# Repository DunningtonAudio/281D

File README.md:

# 281D
A quad function generator project

The 281D Quad Function Generator is designed to replicate the functionality of the Buchla 281 module using modern construction techniques and readily available parts. It is primarily based on the original circuit designed by Don Buchla, with the following additions/alterations:

* Improved input and mode selection circuitry – no requirement to “kick” the generators when selecting self cycle mode.
* All outputs are buffered, protecting the integrator core and passive end pulse generation from the effects of loading when stacked to multiple inputs.
* End pulse outputs are designed to allow stacking of multiple outputs to a single input without affecting cycling of individual generators, allowing the creation of complex/non-repeating/polyrhythmic pulse sequences. Unlike other solutions that simply add a diode in series with the output, the 281D end pulse outputs can drive a floating input low.
 
There are several build options to adjust the function of the module to a particular users requirements.

The repository contains:

* KiCad project files.
* Schematic and build/calibration notes as PDF files.
* Bill of Materials in ODS format.
* Interactive webpage for matching BOM items to PCB locations.

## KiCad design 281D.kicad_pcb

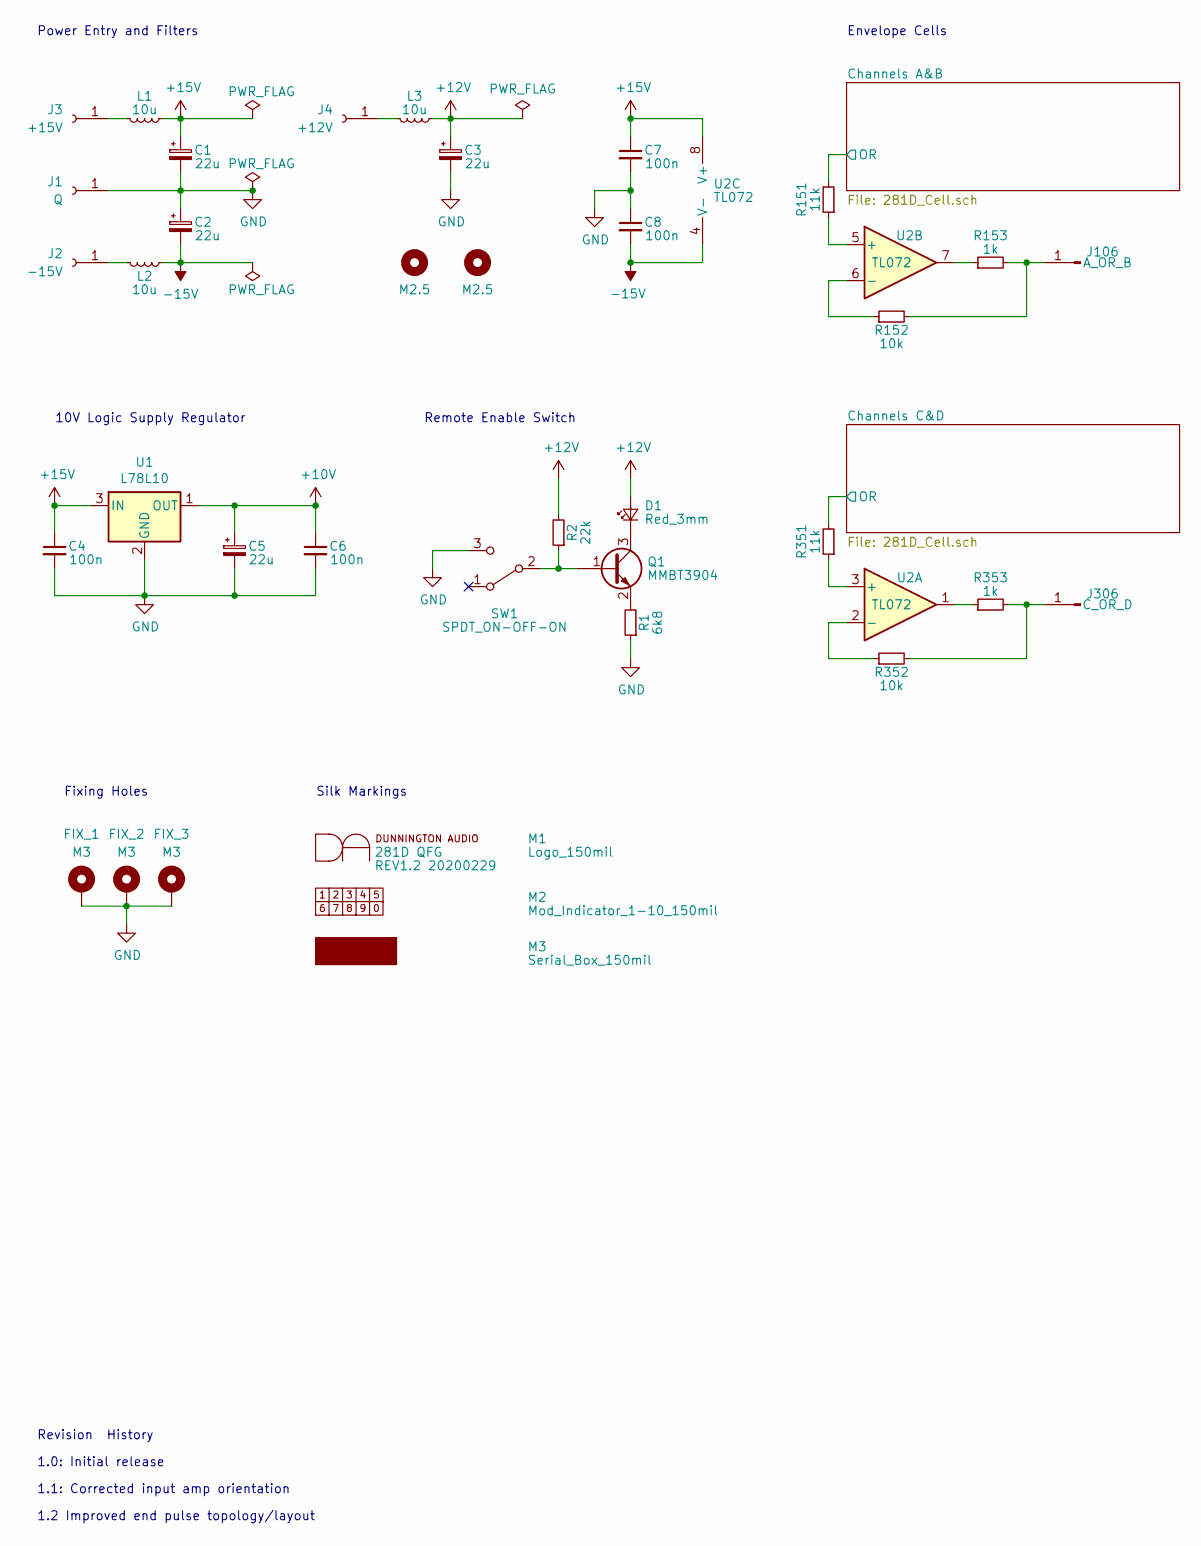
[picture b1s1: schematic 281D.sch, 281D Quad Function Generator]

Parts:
C1, C2, C3, C5: 22u; CP_Elec_5x5.3
C4, C6, C7, C8: 100n; C_0805_2012Metric
D1: Red_3mm; LED_D3.0mm
FIX_1, FIX_2, FIX_3: M3; MountingHole_3.2mm_M3_Pad_Via
H101, H102: M2.5; MountingHole_2.5mm
J1: Q; SolderWirePad_1x01_Drill1.2mm
J2: -15V; SolderWirePad_1x01_Drill1.2mm
J3: +15V; SolderWirePad_1x01_Drill1.2mm
J4: +12V; SolderWirePad_1x01_Drill1.2mm
J106, J306: 108-0910-001; Johnson_108-09XX-001
L1, L2, L3: 10u; L_0805_2012Metric
M1: Logo_150mil
M2: Mod_Indicator_1-10_150mil
M3: Serial_Box_150mil
Q1: MMBT3904; SOT-23
R1: 6k8; R_0805_2012Metric
R2: 22k; R_0805_2012Metric
R151, R351: 11k; R_0805_2012Metric
R152, R352: 10k; R_0805_2012Metric
R153, R353: 1k; R_0805_2012Metric
SW1: SPDT_ON-OFF-ON; M201xSS1x01
U1: L78L10; SOT-89-3
U2: TL072; SOIC-8_3.9x4.9mm_P1.27mm

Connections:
+10V: C5.1, C6.1, U1.1 (OUT); also elsewhere on the board
+12V: C3.1, D1.2 (A), L3.1, R2.2; also elsewhere on the board
+15V: C1.1, C4.1, C7.1, L1.1, U1.3 (IN), U2.8 (V+); also elsewhere on the board
-15V: C2.2, C8.2, L2.1, U2.4 (V-); also elsewhere on the board
/Channels A&B/OR: R151.2; also elsewhere on the board
/Channels C&D/OR: R351.2; also elsewhere on the board
GND: C1.2, C2.1, C3.2, C4.2, C5.2, C6.2, C7.2, C8.1, FIX_1.1, FIX_2.1, FIX_3.1, J1.1, R1.1, SW1.3 (C), U1.2 (GND); also elsewhere on the board
unnamed: D1.1 (K), Q1.3 (C)
unnamed: J2.1, L2.2
unnamed: J3.1, L1.2
unnamed: J4.1, L3.2
unnamed: J106.1, R152.2, R153.2
unnamed: J306.1, R352.2, R353.2
unnamed: Q1.1 (B), R2.1, SW1.2 (B)
unnamed: Q1.2 (E), R1.2
unnamed: R151.1, U2.5 (+)
unnamed: R152.1, U2.6 (-)
unnamed: R153.1, U2.7
unnamed: R351.1, U2.3 (+)
unnamed: R352.1, U2.2 (-)
unnamed: R353.1, U2.1

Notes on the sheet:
Envelope Cells
Power Entry and Filters
10V Logic Supply Regulator
Remote Enable Switch
Fixing Holes
Revision History
1.0: Initial release
1.1: Corrected input amp orientation
1.2 Improved end pulse topology/layout
Silk Markings

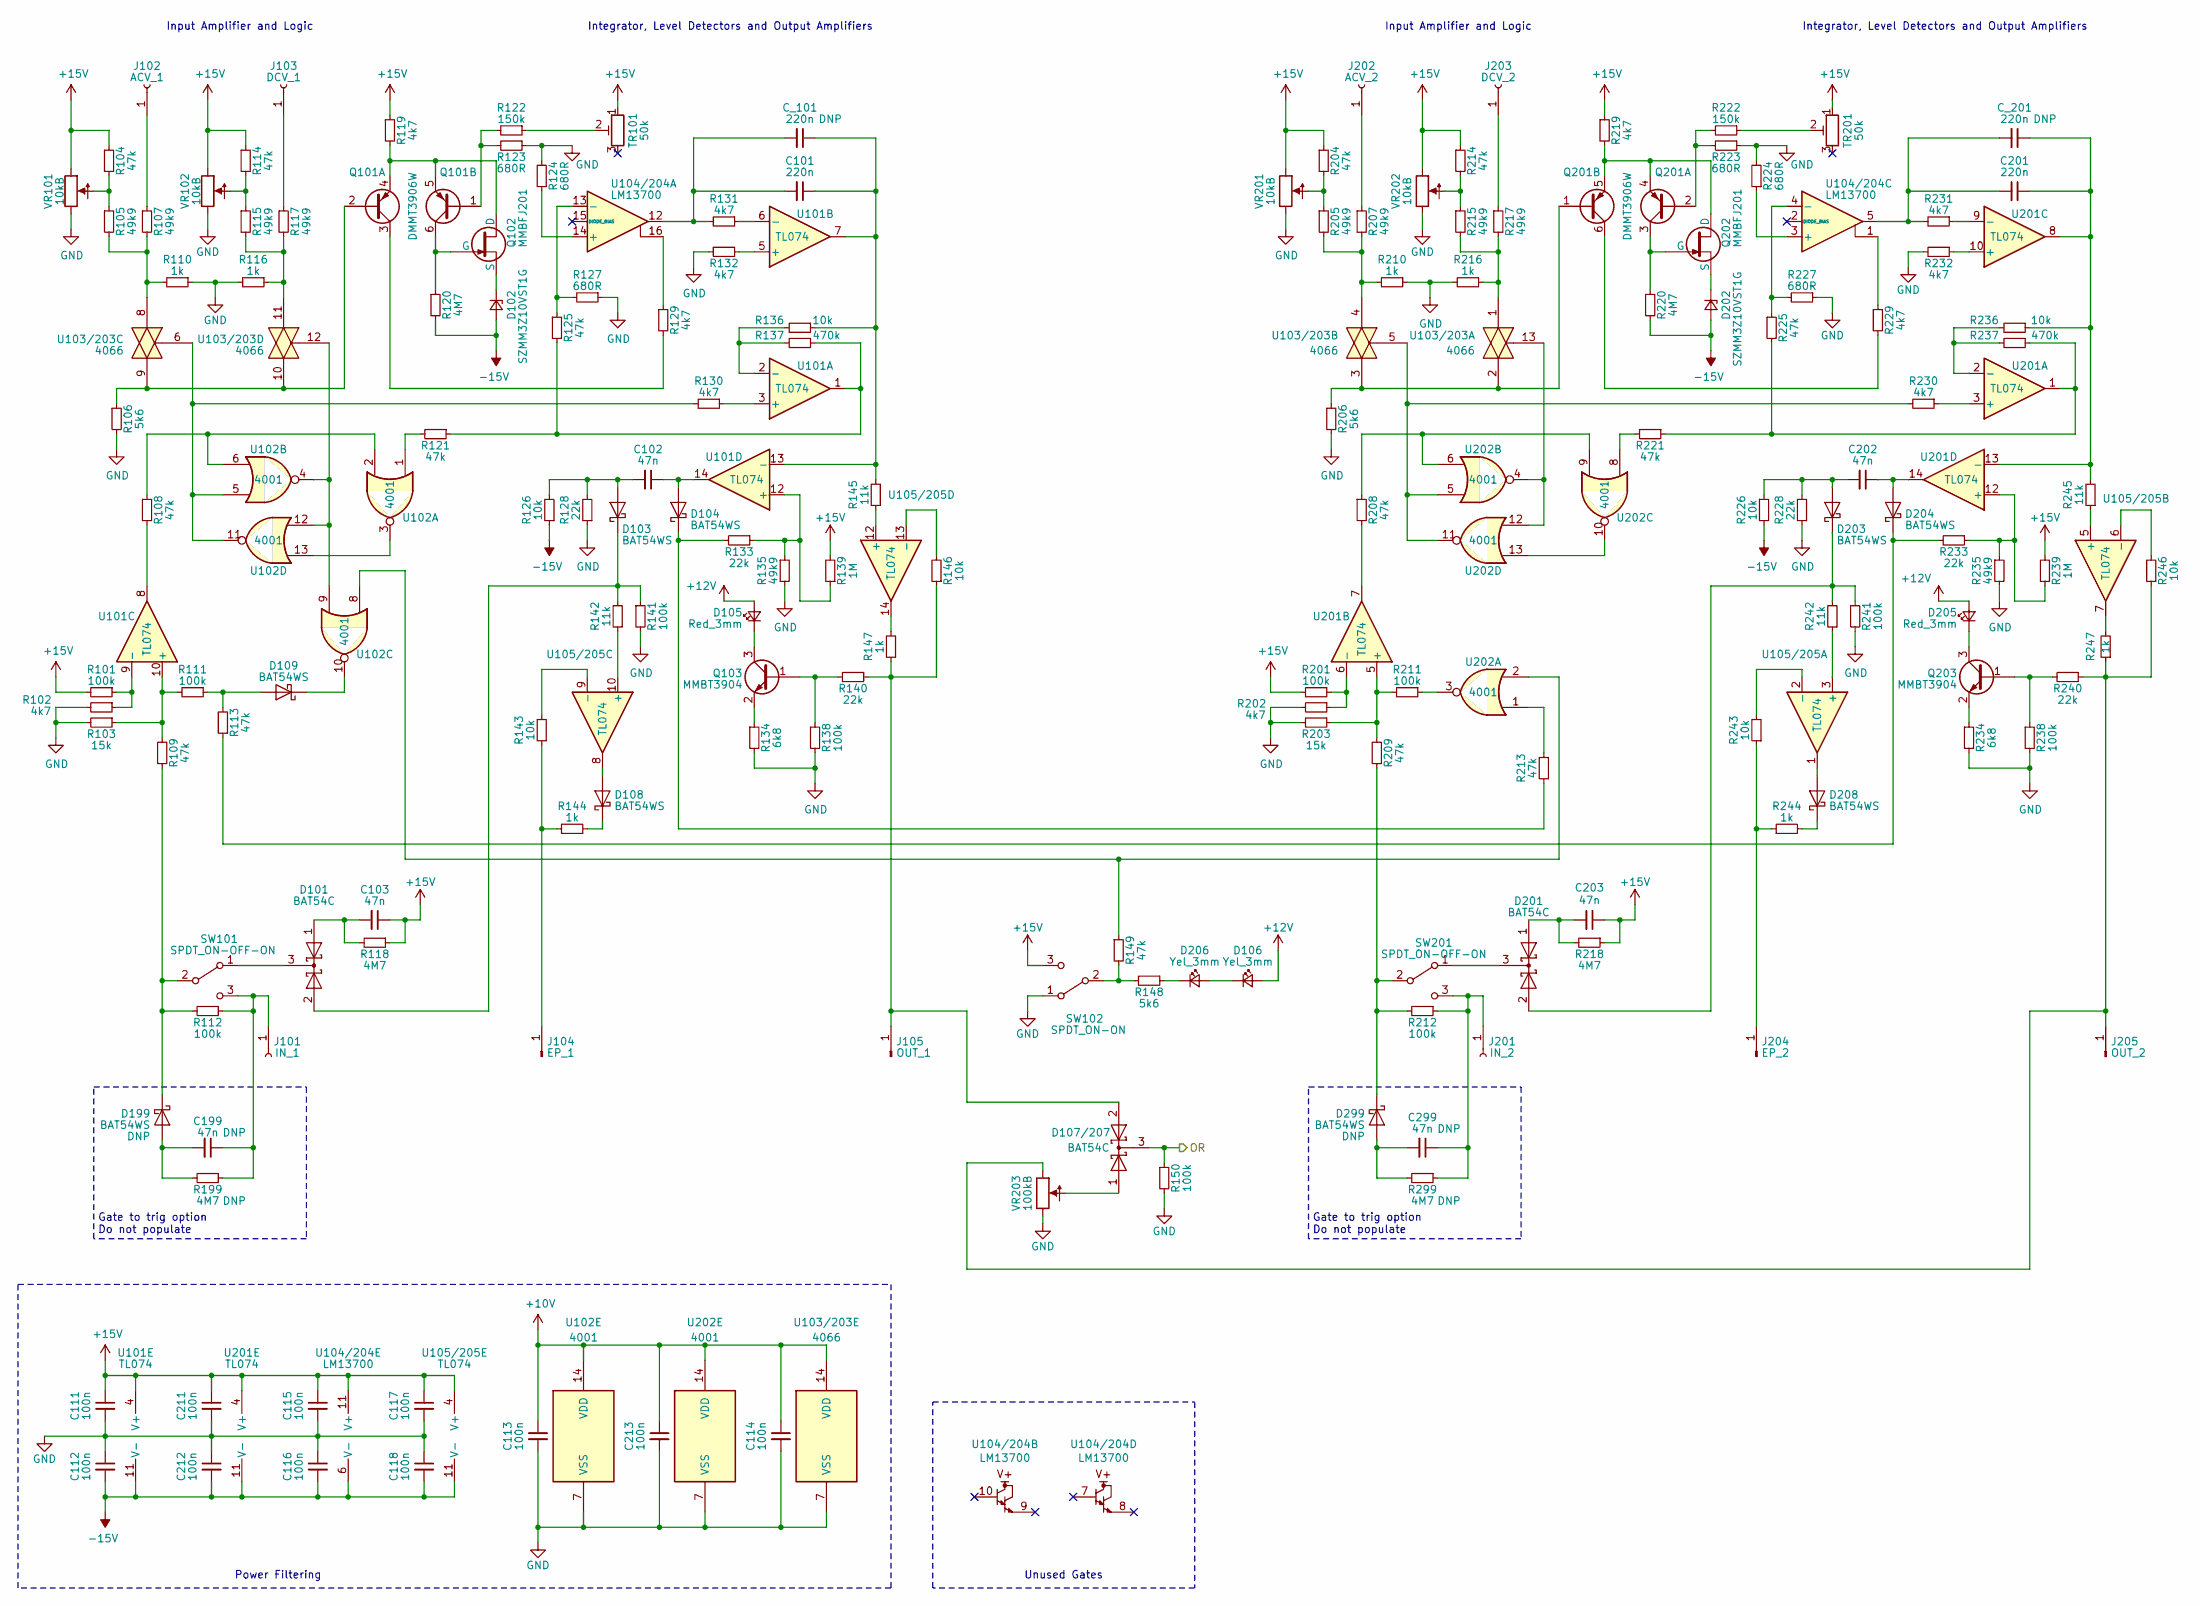
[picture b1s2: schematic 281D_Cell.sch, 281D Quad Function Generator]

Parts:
C101, C201: 220n; C_2416_6041Metric
C102, C103, C199, C202, C203, C299: 47n; C_0805_2012Metric
C111, C112, C113, C114, C115, C116, C117, C118, C211, C212, C213: 100n; C_0805_2012Metric
C_101, C_201: 220n; C_Rect_L7.0mm_W2.5mm_P5.00mm
D101, D107/207, D201: BAT54C; SOT-23
D102, D202: SZMM3Z10VST1G; D_SOD-323
D103, D104, D108, D109, D199, D203, D204, D208, D299: BAT54WS; D_SOD-323
D105, D205: Red_3mm; LED_D3.0mm
D106, D206: Yel_3mm; LED_D3.0mm
J101, J201: 108-0906-001; Johnson_108-09XX-001
J102, J103, J202, J203: 108-0903-001; Johnson_108-09XX-001
J104, J204: 108-0902-001; Johnson_108-09XX-001
J105, J205: 108-0910-001; Johnson_108-09XX-001
Q101, Q201: DMMT3906W; SOT-363_SC-70-6
Q102, Q202: MMBFJ201; SOT-23
Q103, Q203: MMBT3904; SOT-23
R101, R111, R112, R138, R141, R150, R201, R211, R212, R238, R241: 100k; R_0805_2012Metric
R102, R119, R129, R130, R131, R132, R202, R219, R229, R230, R231, R232: 4k7; R_0805_2012Metric
R103, R203: 15k; R_0805_2012Metric
R104, R108, R109, R113, R114, R121, R125, R149, R204, R208, R209, R213, R214, R221, R225: 47k; R_0805_2012Metric
R105, R107, R115, R117, R135, R205, R207, R215, R217, R235: 49k9; R_0805_2012Metric
R106, R148, R206: 5k6; R_0805_2012Metric
R110, R116, R144, R147, R210, R216, R244, R247: 1k; R_0805_2012Metric
R118, R120, R199, R218, R220, R299: 4M7; R_0805_2012Metric
R122, R222: 150k; R_0805_2012Metric
R123, R124, R127, R223, R224, R227: 680R; R_0805_2012Metric
R126, R136, R143, R146, R226, R236, R243, R246: 10k; R_0805_2012Metric
R128, R133, R140, R228, R233, R240: 22k; R_0805_2012Metric
R134, R234: 6k8; R_0805_2012Metric
R137, R237: 470k; R_0805_2012Metric
R139, R239: 1M; R_0805_2012Metric
R142, R145, R242, R245: 11k; R_0805_2012Metric
SW101, SW201: SPDT_ON-OFF-ON; M201xSS1x01
SW102: SPDT_ON-ON; M201xSS1x01
TR101, TR201: 50k; Potentiometer_Bourns_3314J_Vertical
U101, U105/205, U201: TL074; SOIC-14_3.9x8.7mm_P1.27mm
U102, U202: 4001; SOIC-14_3.9x8.7mm_P1.27mm
U103/203: 4066; SOIC-14_3.9x8.7mm_P1.27mm
U104/204: LM13700; SOIC-16_3.9x9.9mm_P1.27mm
VR101, VR102, VR201, VR202: 10kB; RV16AF-41-(L)R1-XXX
VR203: 100kB; RD901F-40-00D

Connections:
+10V: C113.1, C114.1, C213.1, U102.14 (VDD), U103/203.14 (VDD), U202.14 (VDD); also elsewhere on the board
+12V: D105.2 (A), D106.2 (A), D205.2 (A); also elsewhere on the board
+15V: C103.1, C111.1, C115.1, C117.1, C203.1, C211.1, R101.2, R104.1, R114.1, R118.1, R119.1, R139.2, R201.2, R204.1, R214.1, R218.1, R219.1, R239.2, SW102.3 (C), TR101.1, TR201.1, U101.4 (V+), U104/204.11 (V+), U105/205.4 (V+), U201.4 (V+), VR101.3 (1), VR102.3 (1), VR201.3 (1), VR202.3 (1); also elsewhere on the board
-15V: C112.2, C116.2, C118.2, C212.2, D102.2 (A), D202.2 (A), R120.2, R126.1, R220.2, R226.2, U101.11 (V-), U104/204.6 (V-), U105/205.11 (V-), U201.11 (V-); also elsewhere on the board
/Channels A&B/OR: D107/207.3 (K), R150.1; also elsewhere on the board
GND: C111.2, C112.1, C113.2, C114.2, C115.2, C116.1, C117.2, C118.1, C211.2, C212.1, C213.2, R102.2, R103.2, R106.2, R110.1, R116.2, R123.1, R124.2, R127.1, R128.1, R132.2, R134.2, R135.2, R138.2, R141.2, R150.2, R202.2, R203.2, R206.2, R210.1, R216.2, R223.1, R224.2, R227.1, R228.1, R232.2, R234.2, R235.2, R238.2, R241.2, SW102.1 (A), U102.7 (VSS), U103/203.7 (VSS), U202.7 (VSS), VR101.1 (3), VR102.1 (3), VR201.1 (3), VR202.1 (3), VR203.1 (3); also elsewhere on the board
unnamed: C101.1, C_101.1, R136.1, R145.2, U101.7, U101.13 (-)
unnamed: C101.2, C_101.2, R131.2, U104/204.12
unnamed: C102.1, D104.2 (A), U101.14
unnamed: C102.2, D103.2 (A), R126.2, R128.2
unnamed: C103.2, D101.1 (A), R118.2
unnamed: C199.1, J101.1, R112.1, R199.1, SW101.3 (C)
unnamed: C199.2, D199.2 (A), R199.2
unnamed: C201.1, C_201.1, R236.1, R245.2, U201.8, U201.13 (-)
unnamed: C201.2, C_201.2, R231.2, U104/204.5
unnamed: C202.1, D204.2 (A), U201.14
unnamed: C202.2, D203.2 (A), R226.1, R228.2
unnamed: C203.2, D201.1 (A), R218.2
unnamed: C299.1, J201.1, R212.1, R299.1, SW201.3 (C)
unnamed: C299.2, D299.2 (A), R299.2
unnamed: D101.2 (A), D103.1 (K), R141.1, R142.2
unnamed: D101.3 (K), SW101.1 (A)
unnamed: D102.1 (K), Q102.2 (S)
unnamed: D104.1 (K), R133.2, R213.2
unnamed: D105.1 (K), Q103.3 (C)
unnamed: D106.1 (K), D206.2 (A)
unnamed: D107/207.1 (A), VR203.2
unnamed: D107/207.2 (A), J105.1, R140.1, R146.1, R147.1
unnamed: D108.1 (K), R144.2
unnamed: D108.2 (A), U105/205.8
unnamed: D109.1 (K), U102.10
unnamed: D109.2 (A), R111.1, R113.2
unnamed: D199.1 (K), R109.1, R112.2, SW101.2 (B)
unnamed: D201.2 (A), D203.1 (K), R241.1, R242.2
unnamed: D201.3 (K), SW201.1 (A)
unnamed: D202.1 (K), Q202.2 (S)
unnamed: D204.1 (K), R113.1, R233.2
unnamed: D205.1 (K), Q203.3 (C)
unnamed: D206.1 (K), R148.1
unnamed: D208.1 (K), R244.2
unnamed: D208.2 (A), U105/205.1
unnamed: D299.1 (K), R209.1, R212.2, SW201.2 (B)
unnamed: J102.1, R107.1
unnamed: J103.1, R117.1
unnamed: J104.1, R143.1, R144.1
unnamed: J202.1, R207.1
unnamed: J203.1, R217.1
unnamed: J204.1, R243.1, R244.1
unnamed: J205.1, R240.1, R246.1, R247.1, VR203.3 (1)
unnamed: Q101.1 (B2), R122.2, R123.2
unnamed: Q101.2 (B1), R106.1, U103/203.9, U103/203.10
unnamed: Q101.3 (C1), R129.2
unnamed: Q101.4 (E1), Q101.5 (E2), Q102.1 (D), R119.2
unnamed: Q101.6 (C2), Q102.3 (G), R120.1
unnamed: Q103.1 (B), R138.1, R140.2
unnamed: Q103.2 (E), R134.1
unnamed: Q201.1 (B2), R206.1, U103/203.2, U103/203.3
unnamed: Q201.2 (B1), R222.2, R223.2
unnamed: Q201.3 (C1), Q202.3 (G), R220.1
unnamed: Q201.4 (E1), Q201.5 (E2), Q202.1 (D), R219.2
unnamed: Q201.6 (C2), R229.2
unnamed: Q203.1 (B), R238.1, R240.2
unnamed: Q203.2 (E), R234.1
unnamed: R101.1, R102.1, U101.9 (-)
unnamed: R103.1, R109.2, R111.2, U101.10 (+)
unnamed: R104.2, R105.1, VR101.2
unnamed: R105.2, R107.2, R110.2, U103/203.8
unnamed: R108.1, U102.2, U102.6
unnamed: R108.2, U101.8
unnamed: R114.2, R115.1, VR102.2
unnamed: R115.2, R116.1, R117.2, U103/203.11
unnamed: R121.1, R125.2, R137.1, U101.1
unnamed: R121.2, U102.1
unnamed: R122.1, TR101.2
unnamed: R124.1, U104/204.14 (+)
unnamed: R125.1, R127.2, U104/204.13 (-)
unnamed: R129.1, U104/204.16
unnamed: R130.1, U101.3 (+)
unnamed: R130.2, U102.5, U102.11, U103/203.6
unnamed: R131.1, U101.6 (-)
unnamed: R132.1, U101.5 (+)
unnamed: R133.1, R135.1, R139.1, U101.12 (+)
unnamed: R136.2, R137.2, U101.2 (-)
unnamed: R142.1, U105/205.10 (+)
unnamed: R143.2, U105/205.9 (-)
unnamed: R145.1, U105/205.12 (+)
unnamed: R146.2, U105/205.13 (-)
unnamed: R147.2, U105/205.14
unnamed: R148.2, R149.2, SW102.2 (B)
unnamed: R149.1, U102.8, U202.2
unnamed: R201.1, R202.1, U201.6 (-)
unnamed: R203.1, R209.2, R211.2, U201.5 (+)
unnamed: R204.2, R205.1, VR201.2
unnamed: R205.2, R207.2, R210.2, U103/203.4
unnamed: R208.1, U202.6, U202.9
unnamed: R208.2, U201.7
unnamed: R211.1, U202.3
unnamed: R213.1, U202.1
unnamed: R214.2, R215.1, VR202.2
unnamed: R215.2, R216.1, R217.2, U103/203.1
unnamed: R221.1, R225.2, R237.1, U201.1
unnamed: R221.2, U202.8
unnamed: R222.1, TR201.2
unnamed: R224.1, U104/204.3 (+)
unnamed: R225.1, R227.2, U104/204.4 (-)
unnamed: R229.1, U104/204.1
unnamed: R230.1, U201.3 (+)
unnamed: R230.2, U103/203.5, U202.5, U202.11
unnamed: R231.1, U201.9 (-)
unnamed: R232.1, U201.10 (+)
unnamed: R233.1, R235.1, R239.1, U201.12 (+)
unnamed: R236.2, R237.2, U201.2 (-)
unnamed: R242.1, U105/205.3 (+)
unnamed: R243.2, U105/205.2 (-)
unnamed: R245.1, U105/205.5 (+)
unnamed: R246.2, U105/205.6 (-)
unnamed: R247.2, U105/205.7
unnamed: U102.4, U102.9, U102.12, U103/203.12
unnamed: U102.3, U102.13
unnamed: U103/203.13, U202.4, U202.12
unnamed: U202.10, U202.13

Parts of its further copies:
C301, C401: 220n; C_2416_6041Metric
C302, C303, C399, C402, C403, C499: 47n; C_0805_2012Metric
C311, C312, C313, C314, C315, C316, C317, C318, C411, C412, C413: 100n; C_0805_2012Metric
C_301, C_401: 220n; C_Rect_L7.0mm_W2.5mm_P5.00mm
D301, D307/407, D401: BAT54C; SOT-23
D302, D402: SZMM3Z10VST1G; D_SOD-323
D303, D304, D308, D309, D399, D403, D404, D408, D499: BAT54WS; D_SOD-323
D305, D405: Red_3mm; LED_D3.0mm
D306, D406: Yel_3mm; LED_D3.0mm
J301, J401: 108-0906-001; Johnson_108-09XX-001
J302, J303, J402, J403: 108-0903-001; Johnson_108-09XX-001
J304, J404: 108-0902-001; Johnson_108-09XX-001
J305, J405: 108-0910-001; Johnson_108-09XX-001
Q301, Q401: DMMT3906W; SOT-363_SC-70-6
Q302, Q402: MMBFJ201; SOT-23
Q303, Q403: MMBT3904; SOT-23
R301, R311, R312, R338, R341, R350, R401, R411, R412, R438, R441: 100k; R_0805_2012Metric
R302, R319, R329, R330, R331, R332, R402, R419, R429, R430, R431, R432: 4k7; R_0805_2012Metric
R303, R403: 15k; R_0805_2012Metric
R304, R308, R309, R313, R314, R321, R325, R349, R404, R408, R409, R413, R414, R421, R425: 47k; R_0805_2012Metric
R305, R307, R315, R317, R335, R405, R407, R415, R417, R435: 49k9; R_0805_2012Metric
R306, R348, R406: 5k6; R_0805_2012Metric
R310, R316, R344, R347, R410, R416, R444, R447: 1k; R_0805_2012Metric
R318, R320, R399, R418, R420, R499: 4M7; R_0805_2012Metric
R322, R422: 150k; R_0805_2012Metric
R323, R324, R327, R423, R424, R427: 680R; R_0805_2012Metric
R326, R336, R343, R346, R426, R436, R443, R446: 10k; R_0805_2012Metric
R328, R333, R340, R428, R433, R440: 22k; R_0805_2012Metric
R334, R434: 6k8; R_0805_2012Metric
R337, R437: 470k; R_0805_2012Metric
R339, R439: 1M; R_0805_2012Metric
R342, R345, R442, R445: 11k; R_0805_2012Metric
SW301, SW401: SPDT_ON-OFF-ON; M201xSS1x01
SW302: SPDT_ON-ON; M201xSS1x01
TR301, TR401: 50k; Potentiometer_Bourns_3314J_Vertical
U301, U305/405, U401: TL074; SOIC-14_3.9x8.7mm_P1.27mm
U302, U402: 4001; SOIC-14_3.9x8.7mm_P1.27mm
U303/403: 4066; SOIC-14_3.9x8.7mm_P1.27mm
U304/404: LM13700; SOIC-16_3.9x9.9mm_P1.27mm
VR301, VR302, VR401, VR402: 10kB; RV16AF-41-(L)R1-XXX
VR403: 100kB; RD901F-40-00D

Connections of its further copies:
+10V: C313.1, C314.1, C413.1, U302.14 (VDD), U303/403.14 (VDD), U402.14 (VDD); also elsewhere on the board
+12V: D305.2 (A), D306.2 (A), D405.2 (A); also elsewhere on the board
+15V: C303.1, C311.1, C315.1, C317.1, C403.1, C411.1, R301.2, R304.1, R314.1, R318.1, R319.1, R339.2, R401.2, R404.1, R414.1, R418.1, R419.1, R439.2, SW302.3 (C), TR301.1, TR401.1, U301.4 (V+), U304/404.11 (V+), U305/405.4 (V+), U401.4 (V+), VR301.3 (1), VR302.3 (1), VR401.3 (1), VR402.3 (1); also elsewhere on the board
-15V: C312.2, C316.2, C318.2, C412.2, D302.2 (A), D402.2 (A), R320.2, R326.1, R420.2, R426.2, U301.11 (V-), U304/404.6 (V-), U305/405.11 (V-), U401.11 (V-); also elsewhere on the board
/Channels C&D/OR: D307/407.3 (K), R350.1; also elsewhere on the board
GND: C311.2, C312.1, C313.2, C314.2, C315.2, C316.1, C317.2, C318.1, C411.2, C412.1, C413.2, R302.2, R303.2, R306.2, R310.1, R316.2, R323.1, R324.2, R327.1, R328.1, R332.2, R334.2, R335.2, R338.2, R341.2, R350.2, R402.2, R403.2, R406.2, R410.1, R416.2, R423.1, R424.2, R427.1, R428.1, R432.2, R434.2, R435.2, R438.2, R441.2, SW302.1 (A), U302.7 (VSS), U303/403.7 (VSS), U402.7 (VSS), VR301.1 (3), VR302.1 (3), VR401.1 (3), VR402.1 (3), VR403.1 (3); also elsewhere on the board
unnamed: C301.1, C_301.1, R336.1, R345.2, U301.7, U301.13 (-)
unnamed: C301.2, C_301.2, R331.2, U304/404.12
unnamed: C302.1, D304.2 (A), U301.14
unnamed: C302.2, D303.2 (A), R326.2, R328.2
unnamed: C303.2, D301.1 (A), R318.2
unnamed: C399.1, J301.1, R312.1, R399.1, SW301.3 (C)
unnamed: C399.2, D399.2 (A), R399.2
unnamed: C401.1, C_401.1, R436.1, R445.2, U401.8, U401.13 (-)
unnamed: C401.2, C_401.2, R431.2, U304/404.5
unnamed: C402.1, D404.2 (A), U401.14
unnamed: C402.2, D403.2 (A), R426.1, R428.2
unnamed: C403.2, D401.1 (A), R418.2
unnamed: C499.1, J401.1, R412.1, R499.1, SW401.3 (C)
unnamed: C499.2, D499.2 (A), R499.2
unnamed: D301.2 (A), D303.1 (K), R341.1, R342.2
unnamed: D301.3 (K), SW301.1 (A)
unnamed: D302.1 (K), Q302.2 (S)
unnamed: D304.1 (K), R333.2, R413.2
unnamed: D305.1 (K), Q303.3 (C)
unnamed: D306.1 (K), D406.2 (A)
unnamed: D307/407.1 (A), VR403.2
unnamed: D307/407.2 (A), J305.1, R340.1, R346.1, R347.1
unnamed: D308.1 (K), R344.2
unnamed: D308.2 (A), U305/405.8
unnamed: D309.1 (K), U302.10
unnamed: D309.2 (A), R311.1, R313.2
unnamed: D399.1 (K), R309.1, R312.2, SW301.2 (B)
unnamed: D401.2 (A), D403.1 (K), R441.1, R442.2
unnamed: D401.3 (K), SW401.1 (A)
unnamed: D402.1 (K), Q402.2 (S)
unnamed: D404.1 (K), R313.1, R433.2
unnamed: D405.1 (K), Q403.3 (C)
unnamed: D406.1 (K), R348.1
unnamed: D408.1 (K), R444.2
unnamed: D408.2 (A), U305/405.1
unnamed: D499.1 (K), R409.1, R412.2, SW401.2 (B)
unnamed: J302.1, R307.1
unnamed: J303.1, R317.1
unnamed: J304.1, R343.1, R344.1
unnamed: J402.1, R407.1
unnamed: J403.1, R417.1
unnamed: J404.1, R443.1, R444.1
unnamed: J405.1, R440.1, R446.1, R447.1, VR403.3 (1)
unnamed: Q301.1 (B2), R322.2, R323.2
unnamed: Q301.2 (B1), R306.1, U303/403.9, U303/403.10
unnamed: Q301.3 (C1), R329.2
unnamed: Q301.4 (E1), Q301.5 (E2), Q302.1 (D), R319.2
unnamed: Q301.6 (C2), Q302.3 (G), R320.1
unnamed: Q303.1 (B), R338.1, R340.2
unnamed: Q303.2 (E), R334.1
unnamed: Q401.1 (B2), R406.1, U303/403.2, U303/403.3
unnamed: Q401.2 (B1), R422.2, R423.2
unnamed: Q401.3 (C1), Q402.3 (G), R420.1
unnamed: Q401.4 (E1), Q401.5 (E2), Q402.1 (D), R419.2
unnamed: Q401.6 (C2), R429.2
unnamed: Q403.1 (B), R438.1, R440.2
unnamed: Q403.2 (E), R434.1
unnamed: R301.1, R302.1, U301.9 (-)
unnamed: R303.1, R309.2, R311.2, U301.10 (+)
unnamed: R304.2, R305.1, VR301.2
unnamed: R305.2, R307.2, R310.2, U303/403.8
unnamed: R308.1, U302.2, U302.6
unnamed: R308.2, U301.8
unnamed: R314.2, R315.1, VR302.2
unnamed: R315.2, R316.1, R317.2, U303/403.11
unnamed: R321.1, R325.2, R337.1, U301.1
unnamed: R321.2, U302.1
unnamed: R322.1, TR301.2
unnamed: R324.1, U304/404.14 (+)
unnamed: R325.1, R327.2, U304/404.13 (-)
unnamed: R329.1, U304/404.16
unnamed: R330.1, U301.3 (+)
unnamed: R330.2, U302.5, U302.11, U303/403.6
unnamed: R331.1, U301.6 (-)
unnamed: R332.1, U301.5 (+)
unnamed: R333.1, R335.1, R339.1, U301.12 (+)
unnamed: R336.2, R337.2, U301.2 (-)
unnamed: R342.1, U305/405.10 (+)
unnamed: R343.2, U305/405.9 (-)
unnamed: R345.1, U305/405.12 (+)
unnamed: R346.2, U305/405.13 (-)
unnamed: R347.2, U305/405.14
unnamed: R348.2, R349.2, SW302.2 (B)
unnamed: R349.1, U302.8, U402.2
unnamed: R401.1, R402.1, U401.6 (-)
unnamed: R403.1, R409.2, R411.2, U401.5 (+)
unnamed: R404.2, R405.1, VR401.2
unnamed: R405.2, R407.2, R410.2, U303/403.4
unnamed: R408.1, U402.6, U402.9
unnamed: R408.2, U401.7
unnamed: R411.1, U402.3
unnamed: R413.1, U402.1
unnamed: R414.2, R415.1, VR402.2
unnamed: R415.2, R416.1, R417.2, U303/403.1
unnamed: R421.1, R425.2, R437.1, U401.1
unnamed: R421.2, U402.8
unnamed: R422.1, TR401.2
unnamed: R424.1, U304/404.3 (+)
unnamed: R425.1, R427.2, U304/404.4 (-)
unnamed: R429.1, U304/404.1
unnamed: R430.1, U401.3 (+)
unnamed: R430.2, U303/403.5, U402.5, U402.11
unnamed: R431.1, U401.9 (-)
unnamed: R432.1, U401.10 (+)
unnamed: R433.1, R435.1, R439.1, U401.12 (+)
unnamed: R436.2, R437.2, U401.2 (-)
unnamed: R442.1, U305/405.3 (+)
unnamed: R443.2, U305/405.2 (-)
unnamed: R445.1, U305/405.5 (+)
unnamed: R446.2, U305/405.6 (-)
unnamed: R447.2, U305/405.7
unnamed: U302.4, U302.9, U302.12, U303/403.12
unnamed: U302.3, U302.13
unnamed: U303/403.13, U402.4, U402.12
unnamed: U402.10, U402.13

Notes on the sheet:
Unused Gates
Gate to trig option Do not populate
Power Filtering
Input Amplifier and Logic
Integrator, Level Detectors and Output Amplifiers

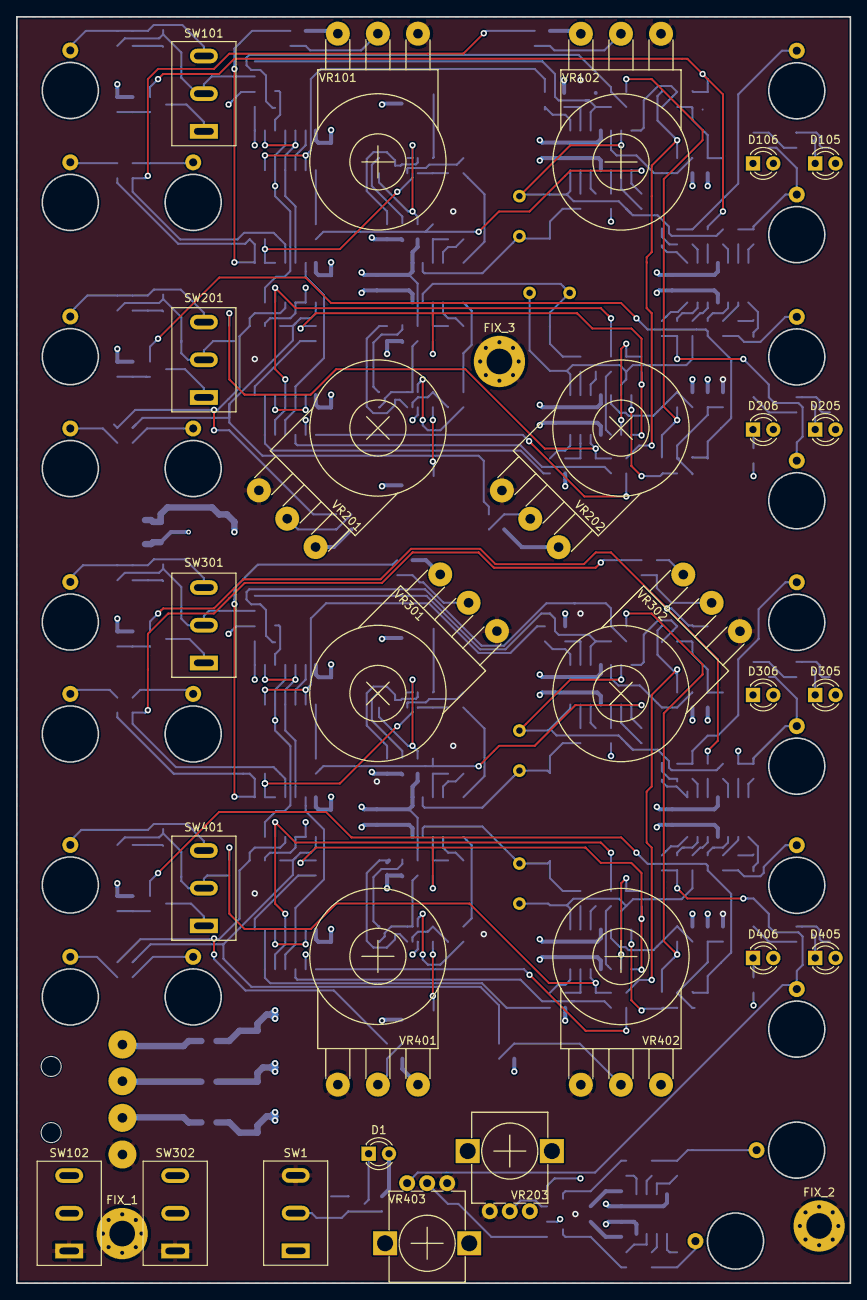
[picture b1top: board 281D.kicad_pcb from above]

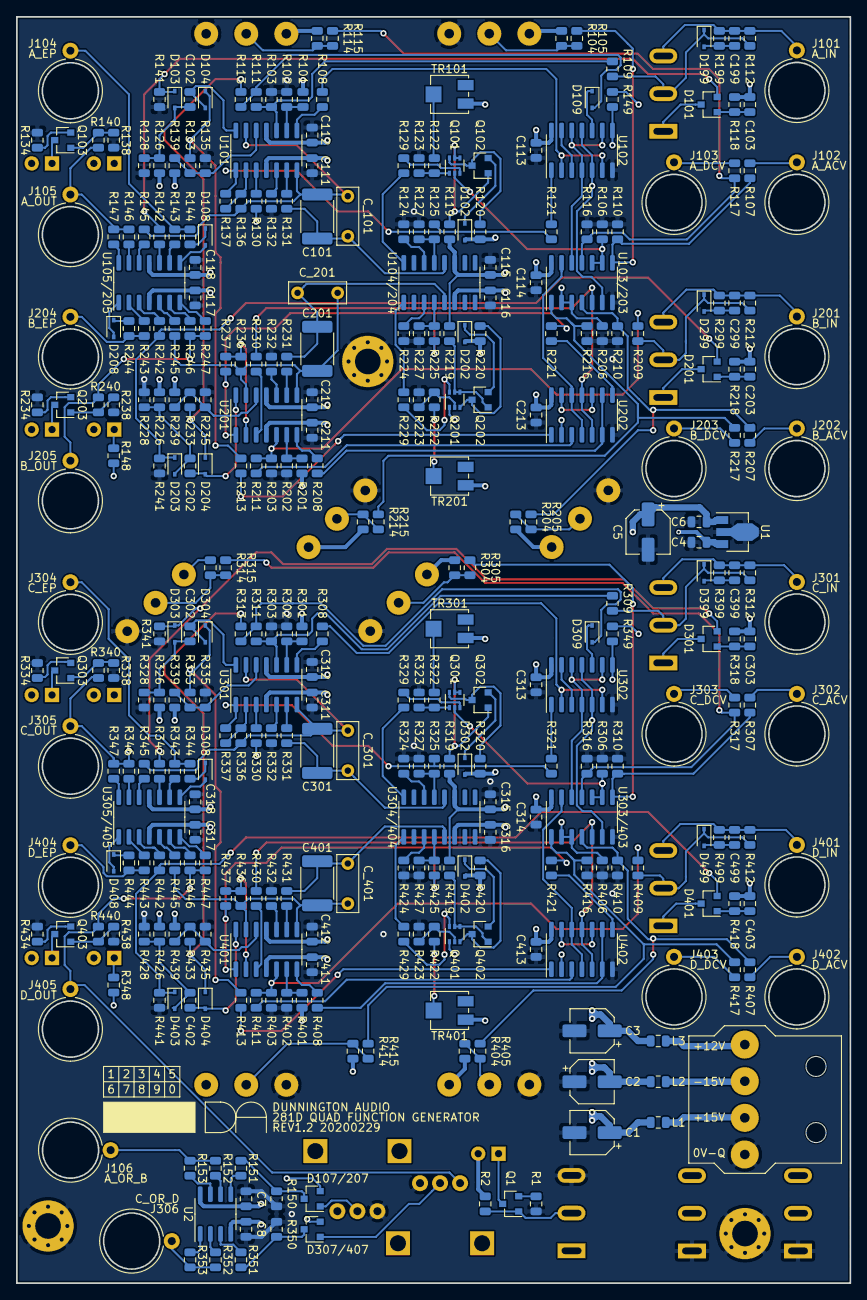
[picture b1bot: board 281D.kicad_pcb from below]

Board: 4 copper layers, 104.0 x 158.0 mm, 380 parts (351 on the bottom side), 251 nets.

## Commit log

2020-05-13 Add .gitignore
2020-05-19 Update .gitignore, update BOM, add BOM pdf.
2020-06-10 Update BOM, BOM pdf, notes. Schematic and assembly guide correction.
2020-06-29 Update BOM, BOM pdf, notes
